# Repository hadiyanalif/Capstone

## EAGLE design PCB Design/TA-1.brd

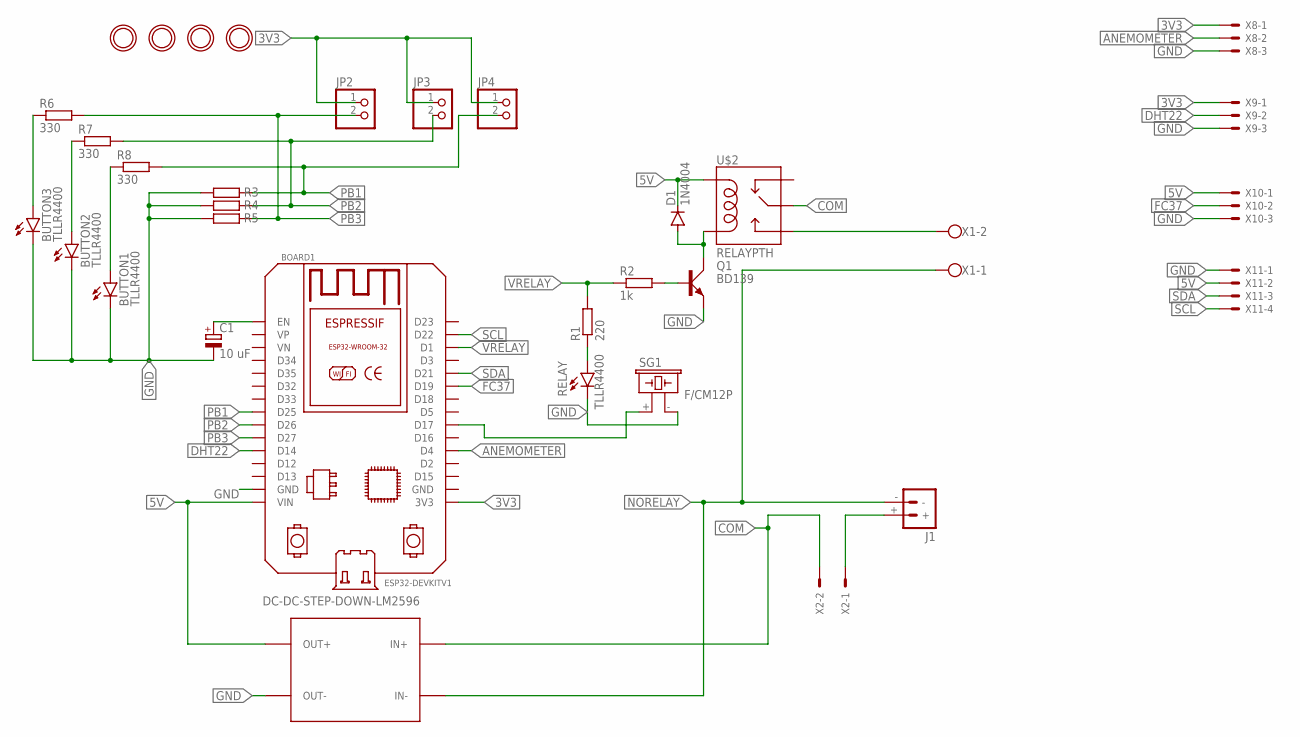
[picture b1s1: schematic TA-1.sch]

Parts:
BOARD1: ESP32DEVKITV1; ESP32-DEVKITV1
BUTTON1, BUTTON2, BUTTON3: TLLR4400; LED3MM
C1: 10 uF; E2,5-5
D1: 1N4004; DO41-10
J1: BATTERY_CONN_DEANS; DEANS
JP2, JP3, JP4: PINHD-1X2; 1X02
Q1: BD139; TO126AV
R1: 220; 0207/10
R2: 1k; 0207/10
R3, R4, R5: R-EU_0207/10; 0207/10
R6, R7, R8: 330; 0207/10
RELAY: TLLR4400; LED3MM
SG1: F/CM12P
U$1, U$4, U$5, U$6: MICROBUILDER_MOUNTINGHOLE3.0THIN; MICROBUILDER_MOUNTINGHOLE_3.0_PLATEDTHIN
U$2: RELAYPTH; SRD-05VDC-SL-C
U$3: DC-DC-STEP-DOWN-LM2596
X1: W237-102
X2: KK-156-2
X8, X9, X10: KK-156-3
X11: KK-156-4

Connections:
3V3: BOARD1.3V3, JP2.1, JP3.1, JP4.1, X8.1, X9.1
5V: BOARD1.VIN, D1.C, U$2.COIL1, U$3.OUT+, X10.1, X11.2
ANEMOMETER: BOARD1.D4, X8.2
COM: U$2.SWCOMMON, U$3.IN+, X2.2
DHT22: BOARD1.D14, X9.2
FC37: BOARD1.D19, X10.2
GND: BOARD1.GND, BUTTON1.K (C), BUTTON2.K (C), BUTTON3.K (C), C1.-, Q1.E, R3.2, R4.2, R5.2, RELAY.K (C), SG1.- (2), U$3.OUT-, X8.3, X9.3, X10.3, X11.1
unnamed: U$2.SWOPEN, X1.2
unnamed: J1.+, X2.1
unnamed: R1.1, RELAY.A
unnamed: BOARD1.EN, C1.+
unnamed: BUTTON3.A, R6.1
unnamed: BUTTON2.A, R7.1
unnamed: BUTTON1.A, R8.1
unnamed: BOARD1.D17, SG1.+ (1)
unnamed: Q1.B, R2.2
unnamed: D1.A, Q1.C, U$2.COIL0
NORELAY: J1.-, U$3.IN-, X1.1
PB1: BOARD1.D25, JP4.2, R3.1, R8.2
PB2: BOARD1.D26, JP3.2, R4.1, R7.2
PB3: BOARD1.D27, JP2.2, R5.1, R6.2
SCL: BOARD1.D22, X11.4
SDA: BOARD1.D21, X11.3
VRELAY: BOARD1.D1, R1.2, R2.1

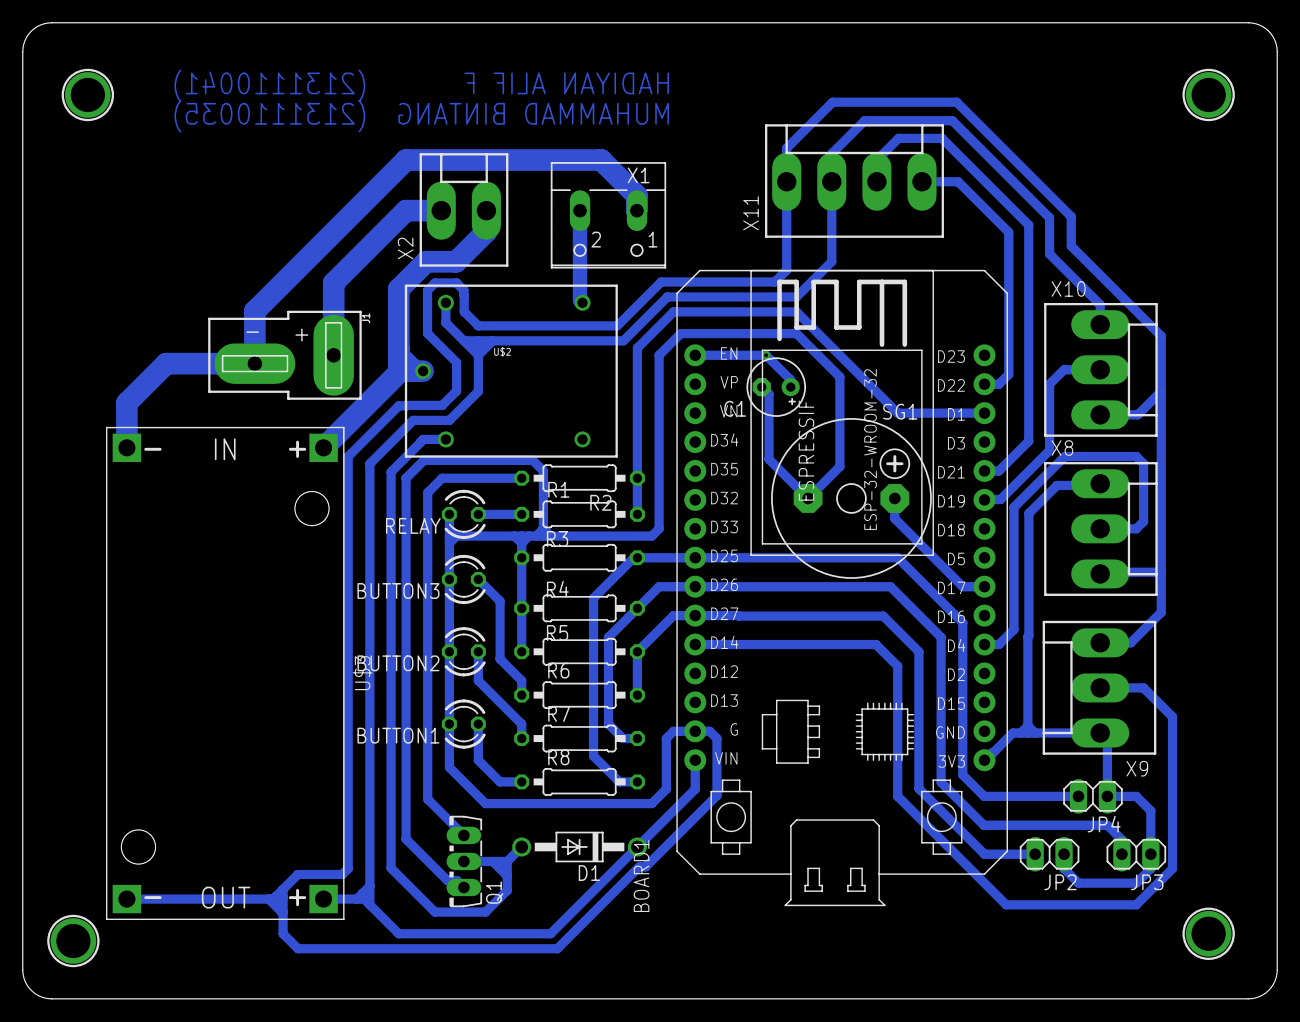
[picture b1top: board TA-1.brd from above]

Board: 2 copper layers, 110.0 x 85.6 mm, 33 parts (0 on the bottom side), 24 nets.

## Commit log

2025-10-07 akhir

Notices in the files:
parts and their libraries:
SparkFun-Connectors: Licensing: Creative Commons ShareAlike 4.0 International - https://creativecommons.org/licenses/by-sa/4.0
0.96inch OLED: Released under the Creative Commons Attribution 4.0 International License: http://creativecommons.org/licenses/by/4.0
